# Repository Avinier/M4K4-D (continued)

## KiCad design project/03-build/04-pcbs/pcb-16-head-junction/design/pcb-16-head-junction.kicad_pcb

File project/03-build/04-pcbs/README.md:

# 04 — PCBs

This folder holds the schematic, layout, fabrication and electrical-validation work for the robot's custom boards. It is a work area, not a fabrication release. Part records stay in the [project BOM](../BOM.csv); every selection and change goes in the [build decisions](../decisions.md). It replaces the former `04-custom-pcb/` folder ([D-038](../decisions.md#d-038)).

Each custom board is designed, procured and integrated into the final CAD one at a time, in its own `pcb-NN-name/` folder. [workflow.md](workflow.md) describes the three stages and tracks each board's progress.

## Tools

Chosen in [D-058](../decisions.md#d-058); layout tool and routing changed by [D-060](../decisions.md#d-060).

| Tool | Used for | Where |
|---|---|---|
| KiCad 10.99 (nightly) + KiPy | Schematic and layout, driven through KiPy and computer-use tools; the GUI for review | `/Applications/KiCad-nightly` (build 20261024, `de08734017`), side by side with 10.0.6 in `/Applications/KiCad`. KiPy (`kicad-python` 0.8.0) in `~/.local/share/kipy/venv`; it talks to the running GUI, and the nightly has no bundled `pcbnew` Python. Each board's project is in its folder's `design/` |
| `kicad-cli` (same install as the layout) | ERC, DRC with the schematic-to-board check, Gerbers, drill, pick-and-place, BOM, board STEP, renders | `/Applications/KiCad-nightly/KiCad.app/Contents/MacOS/kicad-cli` (10.99). The 10.0.6 CLI in `/Applications/KiCad` may not read files the nightly saved |
| [`tools/kp.py`](tools/kp.py) | KiPy layout helpers: place (restores 3D models after a flip), octolinear tracks, vias, audit, DRC. Steps in [design-playbook.md](design-playbook.md) | Run with `~/.local/share/kipy/venv/bin/python` against the open PCB editor |
| JLCPCB (default), PCBWay, Lion Circuits (MII service) | PCB fabrication and assembly (PCBA). These three only. Layouts follow the [fab-neutral rules](#fab-neutral-design-rules), and the fab is chosen by quote ([D-062](../decisions.md#d-062)) | — |
| text-to-cad (cadgen) | Stage 3: the board STEP placed in the robot CAD | Project runtime 0.4.28 (see [final/v1](../final/v1/README.md)) |

## Layout rules

These rules take priority over D-058 ([D-060](../decisions.md#d-060); builder, 2026-10-14). They come from someone else's experience of LLM-driven KiCad layout. When an LLM lays out a board, it must:

1. use KiCad 10.99 (the nightly build, which adds scripting features) and drive it through KiPy and computer-use tools;
2. not use an autorouter such as Freerouting;
3. place components one at a time or in small functional groups;
4. adjust placement after routing where that helps;
5. route with octolinear traces, organised into buses of parallel, equally spaced tracks. Plan fanouts first. Keep detours and roundabout routes to a minimum, especially on signal nets. Size track widths and pours for each net's current. Optionally, write reusable scripts that check these properties and use them to check the work.

## Fab-neutral design rules

Only three fabs make Makad boards: **JLCPCB** (China, the default), **PCBWay** (China) and **Lion Circuits** (Bengaluru), on its **MII** (Make in India) service ([D-062](../decisions.md#d-062), builder, 2026-10-25). Every board is laid out so that any of the three can make it on its standard service, with no layout change. The rule set is the strictest standard 2-layer, 1 oz limit of the three. Each board carries it as a KiCad custom rules file, `design/<board>.kicad_dru`, copied from [PCB-15's](pcb-15-nose-hall/design/pcb-15-nose-hall.kicad_dru). The fab is chosen by quote at procure.

| Rule | Fab-neutral minimum | JLCPCB | PCBWay | Lion Circuits MII |
|---|---|---|---|---|
| Track width and copper gap | **0.16 mm** | 0.10 | 0.10 | 0.152 (6 mil) |
| Via | **0.35 mm hole, 0.67 mm pad** (ring 0.16) | hole 0.15, pad 0.25 | hole 0.15, ring 0.15 | drill 0.35, ring 0.152 |
| Via to other copper | **0.31 mm**, from the via's copper and from its hole | — | — | 12 mil (0.305), via to trace |
| Hole to hole | **0.31 mm** | — | — | 12 mil between vias |
| Copper to routed edge | **0.3 mm** | 0.2 | 0.25 | 0.3 |
| Solder-mask web between pads | **0.16 mm** | 0.10 | not stated; confirm | 0.152 |
| Silkscreen text | **1.0 mm high, 0.16 mm line**, or leave silkscreen off | 1.0 | 0.8 | 0.58, line 0.152 |
| Board thickness tolerance | **State it on the order** when the mounting needs it | ±10 % | ±10 % at 1.0 mm and thicker; confirm below | ±10 % |
| Assembly, minimum board | **Panelise** small boards | 10 × 10 mm | quote; 0402 parts get an engineering review | 50 × 100 mm |

Lion's page lists three services. **MII** is the target. **Custom** is looser (0.25 mm drill, 10 mil via spacing), so an MII layout also suits it. **Rush** is tighter (0.4 mm drill, 8 mil tracks, 14 mil via spacing) and is not a target. A board that needs Rush is checked against it first.

Sources, read 2026-10-25: [JLCPCB](https://jlcpcb.com/capabilities/pcb-capabilities), [PCBWay](https://www.pcbway.com/capabilities.html), [Lion Circuits](https://lioncircuits.com/pcb-manufacturing-capabilities). Read the pages again before each order. If a fab tightens a limit, tighten the rule here first.

## Board register

**[D-093](../decisions.md#d-093) (2026-11-06):** PCB-02, 03, 04, 05, 06 and 07 are replaced by bought modules and PCB-13 is deleted. After D-107 the custom boards are PCB-08, 09, 10, 11, 12 and 15, plus PCB-17 from D-117 (**seven designs**). The superseded rows are kept as the record. The change map is in [simplification-plan.md](../simplification-plan.md).

| ID | Board | Location | BOM | Status | Work still required |
|---|---|---|---|---|---|
| PCB-01 | 2S pack protection | Chassis tub, on the pack | CH-023 | **Bought:** Robocraze TIFPS0629 ([D-019](../decisions.md#d-019)); the RP-02 custom design is reference only | Bench acceptance before cells: [power-boards.md §3](power-boards.md#3-pcb-01--tifps0629-acceptance-before-cells-are-connected) |
| PCB-02 | Charger (BQ25798), on/off latch, pack sense, `ENERGY_OK` | Body, behind the rear panel (vertical) | CH-041 | **Superseded by [D-093](../decisions.md#d-093): bought.** A pushbutton power switch module and an INA226/219 voltage/current monitor; no charger (the pack is charged outside the robot). Rev A routing archived in the [board folder](pcb-02-charger/README.md) | Module selection and India stock ([plan level 3](../simplification-plan.md#7-levels-of-work)) |
| PCB-03 | Motor gate, permit chain, head 5 V rail, drive feeds | Body, above the tub | CH-042 | **Superseded by [D-093](../decisions.md#d-093): bought.** Two buck-boost modules: head pitch/roll 5.5 V and yaw 11.1 V. Drive feeds come straight from the switched bus with the SMBJ8.5A and bulk at each `VM`; the yaw servo plug moves to PCB-08 | Module selection and India stock |
| PCB-04 | Five branch converters (C2, base, Pi, display, audio) | Body, under the compute tray | CH-043 | **Superseded by [D-093](../decisions.md#d-093): bought.** Two Pololu S13V30F5 5 V buck-boost modules ([D-094](../decisions.md#d-094)): one for the Pi, one shared by C3, amp, C2 and display | Module selection and India stock; series Schottky in `W11` (C3 USB back-feed) |
| PCB-05 | Audio front end (MAX98357A, 2 × ADAU7002) | Body, above the Pi, hung from the frame on three M2 SMT spacers ([D-067](../decisions.md#d-067)) | BO-002 | **Superseded by [D-093](../decisions.md#d-093): bought.** MAX98357A breakout (BO-007, promoted from bench) and an audio hub. Rev A archived in the [board folder](pcb-05-audio-front-end/README.md) | Amp mount in CAD; four-mic I²S overlay on the bench |
| PCB-06 ×4 | PDM microphone board | Body shell bosses | BO-005 | **Superseded by [D-093](../decisions.md#d-093): bought.** Four I²S mic breakouts with an L/R pin (INMP441 class), two per lane on SDI0/SDI1. Rev A archived in the [board folder](pcb-06-pdm-mic/README.md) | Boss redesign for the breakout outline; overlay bench test before the shell is printed |
| PCB-07 | Base IMU (ICM-42688-P) | Chassis | CH-021 | **Superseded by [D-093](../decisions.md#d-093): bought.** SPI 6-axis IMU breakout on the existing `J10-7` pinout, on a printed adapter on the J15A holes | Breakout selection; adapter in CAD |
| PCB-08 | W47 body junction, D-107 | Body under yaw plate | CH-083 | **Rev B draft, do not order**: Micro-Fit2×3 and GH6 replace both FFC sockets; 34×25mm, four layers; ERC0/0, pin audit12/12, W47 audit5/5, DRC0 errors/0 unconnected/0 parity (six explained library warnings) | Populated fit, cradle/service checks and physical release gates in [board record](pcb-08-yaw-junction/README.md) |
| PCB-14 | **Superseded by [D-107](../decisions.md#d-107), do not order.** Yaw rotor joiner boards ([D-052](../decisions.md#d-052); replaces the D-044 Ø35 ring): three identical vertical 0.8 mm boards (a fourth identical board joins the CSI on the [D-105](../decisions.md#d-105) camera-loop bracket), each a straight-through 22-pin 0.5 mm FFC joiner ([D-101](../decisions.md#d-101): lower contact *n* → upper 23 − *n*) with a down-facing FH34SRJ for its cassette FFC (`W37`/`W42`/`W43`) and an up-facing one for the head FFC, both on the +Y face; 4.5 mm pitch (D-101); tabs seat in the rotor posts | Body, inside the rotating yaw hub (Z 133.9–150.7) | BO-062 (×3) | Rev A draft (do not order) | FH34SRJ sample: open-actuator height (`E` 3.4 mm); fold mock-up at the 4.5 mm planes; standard-mini CSI end in FH34SRJ and the BO-050 CSI test; CSI Pi-end conductor 1 when the drop is drawn; stage-3 board replacement |
| PCB-09 | C0 link adapter (2 × RS-422, audio pass-through, enclosure-fan switch `J9-4`) | Body, on the Pi header, on two M2.5 × 11 standoffs at Pi holes 3/4 | CH-084 | **Rev B routed and CAD fitted on `pcb-09-revB`; not released** ([D-092](../decisions.md#d-092), [D-098 amendment](../decisions.md#d-098)): Samtec SSW-120-01-T-D socket, 4 layers, retained rev A functions and connector pinouts, plus J6 six-net button/OFF/INA226 `i2c-gpio` service interface; [board folder](pcb-09-c0-link-adapter/README.md). Final CAD uses the rev B STEP | Nightly DRC 0/0/0, fit 8/8, mount 7/7 and final integration PASS. `fab/revB` is a draft; wait for #2813, Pi-image and populated bench acceptance before the D-064 order. CR-02 boot/overlay and fan current, socket seating, contact check and harness pull test remain |
| PCB-10 | C3 controller carrier (watchdog, READY, sleep gate, Hall and TCRT circuits) | Body, −Y side wall | CH-044 | **Inputs frozen** ([D-068](../decisions.md#d-068), [board folder](pcb-10-c3-carrier/README.md)): two screws and two printed edge hooks, Espressif DevKitC-1 v1.1 only, TPS3436CCCBG from Mouser India, GPIO map v0.2, `J10-2` named by direction ; [KiCad geometry installed in final CAD](../final/v1/README.md#pcb-geometry-in-the-whole-robot-assembly) | **Design done, rev A** (four layers; DRC clean; `check_pcb10_fit.py` 7/7; [fab outputs](pcb-10-c3-carrier/fab/revA/README.md)); GPIO map v0.3, `J10-2` in U2's order; U2/U3 from Mouser India, consigned; nose, TCRT and head-riser harness re-routes at stage 3; [D-093](../decisions.md#d-093): `J10-12` is unused (PCB-03 is gone) and `W11` gets a series Schottky against USB back-feed; no re-spin |
| PCB-11 | Status LED carrier (WS2812B-2020-V6, 100 nF, 330 Ω in DIN) | Head crown, in the socket fused inside the crown ([D-065](../decisions.md#d-065)) | CH-085 | **Rev A designed** ([D-065](../decisions.md#d-065)); [board folder](pcb-11-status-led/README.md) ; [KiCad geometry installed in final CAD](../final/v1/README.md#pcb-geometry-in-the-whole-robot-assembly) | Procure: panel (with PCB-15), two-sided assembly quote, passive MPNs, V6 from the fab (C52917434) or an RFQ to Hubtronics; brightness, stray-light and light-bleed bench (G03) |
| PCB-12 | C2 head carrier (ESP32-S3-Zero, servo bus, head-link and display transceivers) | Head, roll frame, in place of the C2 tray | CH-086 | **Rev A draft (do not order)** ([D-102](../decisions.md#d-102)): signals only on three GH headers; head grounds join here through 0 Ω links; replaces the tray's front wall, two M2 screws into crossbar bosses; fit 7/7 through the roll/pitch envelope | Received Zero pad/pin check; ST3215-HS bus levels (B5); the head-harness FFC-to-wire break; stage-3 board replacement |
| PCB-15 | Nose Hall carrier (DRV5055A3, decoupling, output filter, three wire pads); numbered by [D-057](../decisions.md#d-057), formerly listed by its BOM ID | Chassis nose, in the pod-seat slot | CH-064 | **Rev A designed** ([D-013](../decisions.md#d-013), [D-059](../decisions.md#d-059), [D-063](../decisions.md#d-063)); [nose-hall-board.md](../01-chassis/v1/research/nose-hall-board.md); [board folder](pcb-15-nose-hall/README.md) ; [KiCad geometry installed in final CAD](../final/v1/README.md#pcb-geometry-in-the-whole-robot-assembly) | Procure: panel, two-sided assembly quote, passive MPNs; cap trip and wire-break fault bench |
| PCB-16 | **Superseded by [D-107](../decisions.md#d-107), do not order.** Head junction: passive FFC-to-wire break for the W42/W43 head FFCs (two FH34SRJ, per-net wire pads) ([D-103](../decisions.md#d-103)) | Head, flat on the yaw disc beside the +Y leg foot | CH-111 | **Rev A draft (do not order)**: historical fit7/7; removed from final CAD by D107 | Wire-bundle routes across pitch and roll; CSI path; FFC strip mock-up; pad sizes against received wire |
| PCB-17 | Balance-tap fuse cards ×2 (three 1206 1 A very-fast fuses, wire pads) | Chassis tub, on the PCB-01 BMS ends under CH-106 reliefs | CH-103 | **Rev A designed** ([D-117](../decisions.md#d-117)); [board folder](pcb-17-balance-fuse-cards/README.md): ERC 0/0, audit 13/13, parity DRC 0/0/0; two 0.8 mm cards, 6 × 9 and 9.5 × 10 mm | Procure: panel with PCB-11/15; received HW-391 pad and height check; N5 with the cards potted |
| PCB-13 | Charge inlet: GCT USB4140, TVS2200, ESDA25W, STUSB4500, input P-FET | Body, rear-panel pad (comes off with the panel) | BO-015 | **Deleted by [D-093](../decisions.md#d-093).** The pack is charged outside the robot through rear-panel charge and balance ports. Rev A archived in the [board folder](pcb-13-charge-inlet/README.md) | — |

Power-board specification (superseded by [D-093](../decisions.md#d-093) except the DRV8833 facts, the `VM` TVS and the TIFPS0629 acceptance): the RP-02 [board-specs.md](../../02-prototypes/RP-02-electrical/board-specs.md) is the read-only reference, and [power-boards.md](power-boards.md) holds what the build changes. The charge path, from the USB-C inlet to the pack entry, is in [charge-path.md](charge-path.md). Open board work without another home is tracked in [open-items.md](open-items.md).

## Rules

The board outlines in CAD are packaging assumptions. They imply no Gerbers, completed schematic or passed board test.

Basic chassis fit and controlled motor tests can use a regulated bench supply, a development controller, driver boards and a temporary harness. Hall and bare-TCRT circuits can be prototyped separately. Full custom-board fabrication is not a prerequisite for those tests. Battery-powered and integrated sensor/control tests keep their protection, interface and validation requirements.

Before releasing any board, record:

- its exact revision, schematic, BOM and layout;
- connector pinout, protection and enable behaviour;
- mounting dimensions and fabrication/assembly outputs;
- measured electrical results.

When an interface changes, update the affected CAD and the canonical BOM.

**Droid CAD changes go in [final/v1/cad](../final/v1/cad/) only** (builder, 2026-10-14). Envelope fixes, board STEPs that replace placeholders, and the mounting features they need are made in `makad-v1.step.py`. For example, `DROID_CUTS` cuts material from printed parts, `DROID_ADDS` adds it and `DROID_MOVES` shifts parts ([D-063](../decisions.md#d-063)). They are not made in the chassis, body or head sources. The subsystem checks don't see these changes, so each one gets its own targeted check script in `final/v1/cad` (for example `check_pcb15_relief.py`, [D-059](../decisions.md#d-059)).

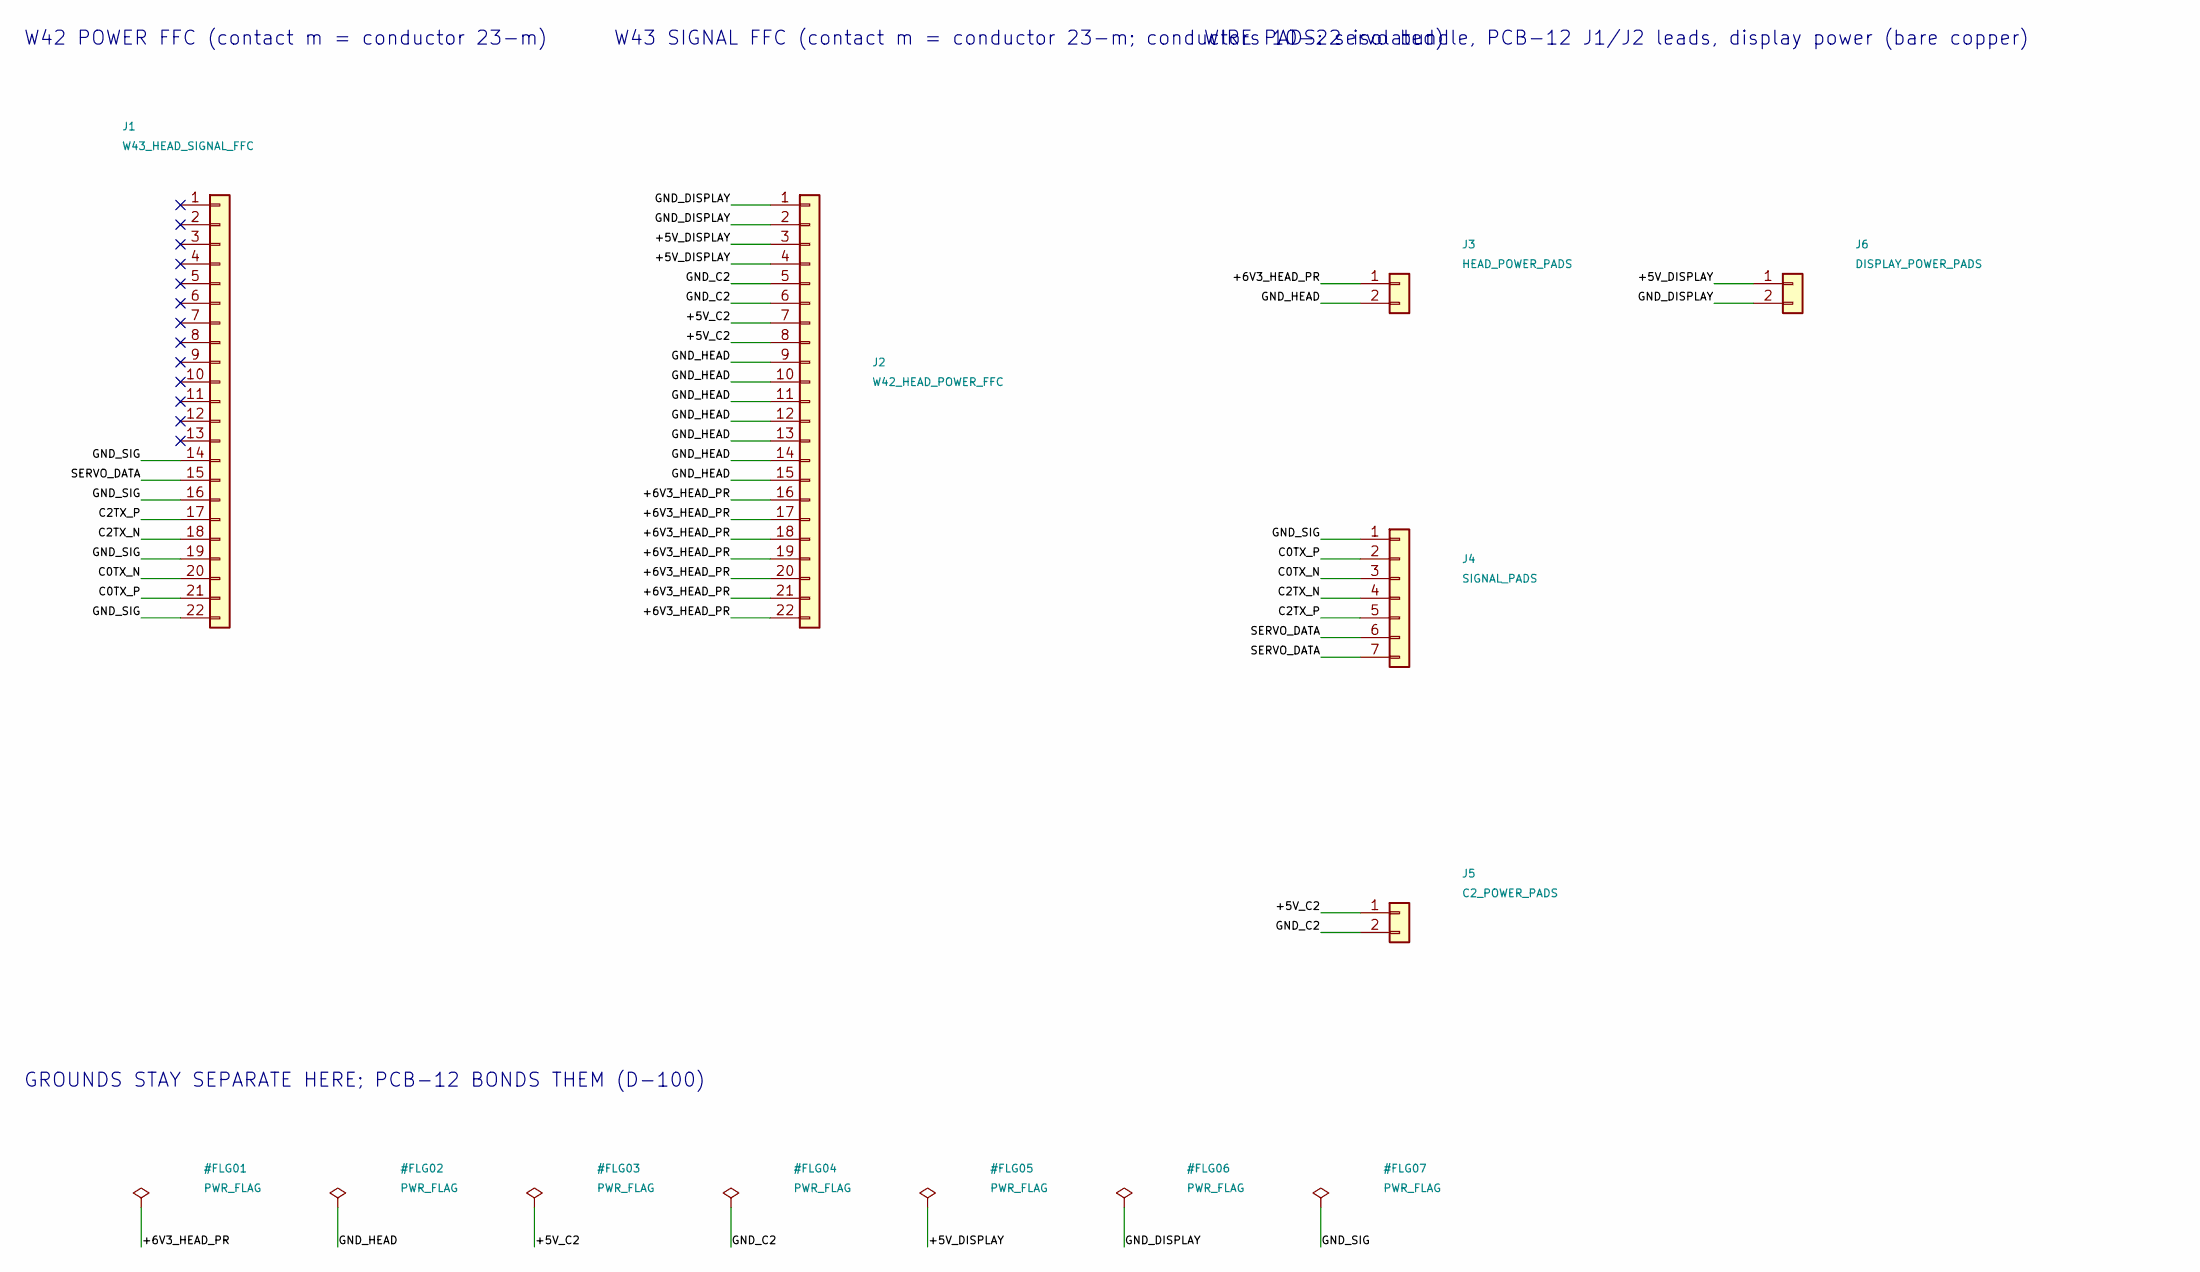
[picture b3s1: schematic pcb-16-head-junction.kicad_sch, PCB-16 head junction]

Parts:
J1: W43_HEAD_SIGNAL_FFC; Hirose_FH34SRJ-22S-0.5SH_1x22_P0.50mm
J2: W42_HEAD_POWER_FFC; Hirose_FH34SRJ-22S-0.5SH_1x22_P0.50mm
J3: HEAD_POWER_PADS; WirePads_Power_1x02_P3.5mm
J4: SIGNAL_PADS; WirePads_1x07_P1.5mm
J5: C2_POWER_PADS; WirePads_1x02_P1.5mm
J6: DISPLAY_POWER_PADS; WirePads_1x02_P1.5mm

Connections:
/+5V_C2: J2.7, J2.8, J5.1
/+5V_DISPLAY: J2.3, J2.4, J6.1
/+6V3_HEAD_PR: J2.16, J2.17, J2.18, J2.19, J2.20, J2.21, J2.22, J3.1
/C0TX_N: J1.20, J4.3
/C0TX_P: J1.21, J4.2
/C2TX_N: J1.18, J4.4
/C2TX_P: J1.17, J4.5
/GND_C2: J2.5, J2.6, J5.2
/GND_DISPLAY: J2.1, J2.2, J6.2
/GND_HEAD: J2.9, J2.10, J2.11, J2.12, J2.13, J2.14, J2.15, J3.2
/GND_SIG: J1.14, J1.16, J1.19, J1.22, J4.1
/SERVO_DATA: J1.15, J4.6, J4.7

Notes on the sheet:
W42 POWER FFC (contact m = conductor 23-m)
W43 SIGNAL FFC (contact m = conductor 23-m; conductors 10-22 isolated)
WIRE PADS: servo bundle, PCB-12 J1/J2 leads, display power (bare copper)
GROUNDS STAY SEPARATE HERE; PCB-12 BONDS THEM (D-100)

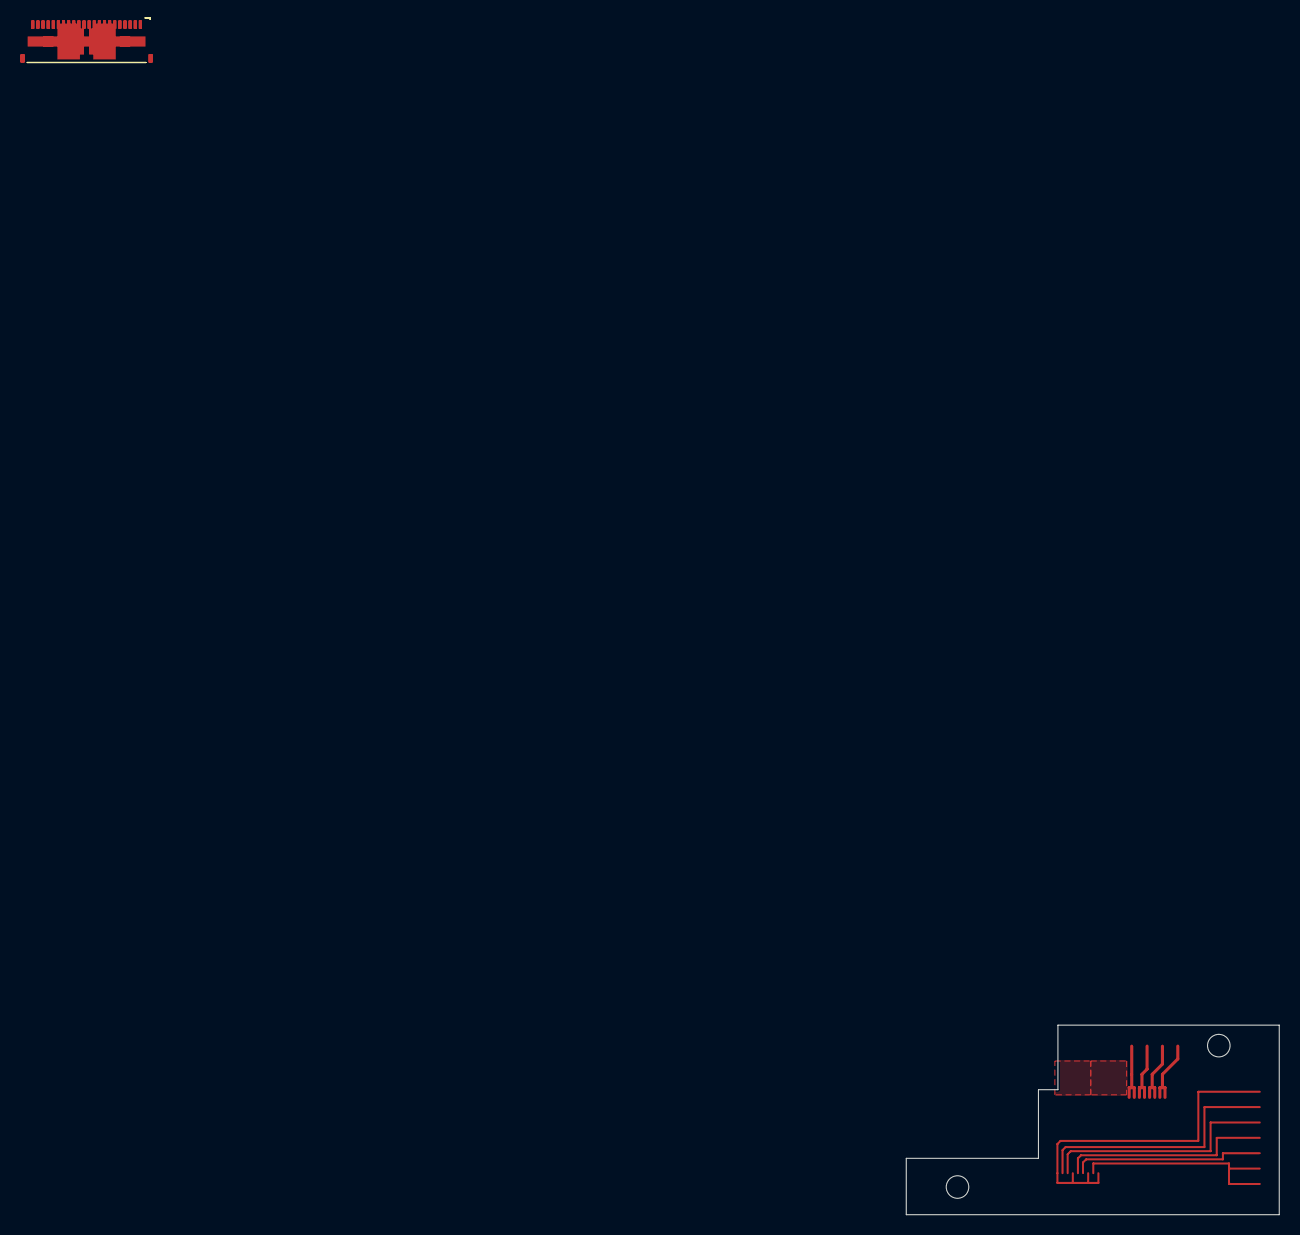
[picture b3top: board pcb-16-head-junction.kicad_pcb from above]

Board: 2 copper layers, 36.4 x 18.5 mm, 6 parts (0 on the bottom side), 12 nets.

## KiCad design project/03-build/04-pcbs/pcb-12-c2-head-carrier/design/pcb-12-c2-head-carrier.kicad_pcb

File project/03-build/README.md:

# 03 — Build

Turn the [prototype decisions](../02-prototypes/) into parts that can be printed, assembled, measured, and revised. This phase is complete when the built robot passes its integration tests, not when the CAD looks finished.

## Status (2026-11-12)

The build follows the [D-093](decisions.md#d-093) simplification: bought power modules replace the charger, motor-gate, converter, audio, mic and IMU boards. Progress by level is in the [simplification plan §7](simplification-plan.md#7-levels-of-work).

- **Modules** selected ([D-094](decisions.md#d-094), [module-selection.md](module-selection.md)) and **ordered 2026-11-08**; each still has a bench gate (N1–N12).
- **Droid CAD** for the modules, ports and mounts is done ([D-095](decisions.md#d-095)); the chassis front module and the D-095 mount prints are re-exported to [04-print](../04-print/01-chassis/README.md) ([D-099](decisions.md#d-099)).
- **Harness**: [05-harness](05-harness/README.md) is **released for build with conditions** ([D-108](decisions.md#d-108), lifting the [D-096](decisions.md#d-096) electrical HOLD): W02P balance taps stay unbuilt until CH-103 protection, no R010 in the switched-bus path, and one closed-body M1 heat check at first power-up.
- **Custom boards** ([04-pcbs](04-pcbs/README.md)): Seven custom designs: PCB-08/09 rev B, PCB-10/11/12/15 rev A and PCB-17 rev A (CH-103 balance-tap fuse cards, D-117). PCB-14/16 are superseded. [D-107](head-umbilical-plan.md) uses twelve loose wires and stripped HDMI pairs through the yaw axis, two B0091 adapters, and the restored D-051 pivot. Draft fabrication and physical acceptance remain HOLD. See the [execution evidence](final/v1/d107-execution.md).
- **BOM**: [BOM.csv](BOM.csv) is reconciled to D-093–D-097; the subsystem BOM snapshots still predate D-093.

## Where things are

| Record | Holds |
|---|---|
| [decisions.md](decisions.md) | The ledger: every decision, part selection, BOM change and CAD edit |
| [BOM.csv](BOM.csv) | The single parts register |
| [BOM-deliveries.md](BOM-deliveries.md) | What has physically arrived, mapped to BOM rows, with problems found |
| [TODO.md](TODO.md) | Open ordering, receiving and release actions |
| [simplification-plan.md](simplification-plan.md) | The D-093 change map, levels of work and bench register (N-tests) |
| [module-selection.md](module-selection.md) | Bought modules (M1–M13) and their acceptance gates |
| [01-chassis](01-chassis/), [02-body](02-body/), [03-head](03-head/) | Subsystem specs, BOM snapshots and subsystem-only CAD |
| [04-pcbs](04-pcbs/README.md) | Custom board register, design workflow and playbook |
| [04-software](04-software/firmware-requirements.md) | Firmware requirements (low-battery stop, button-off, servo limits, mics) |
| [05-harness](05-harness/README.md) | Connectors, cables, pinouts and service breaks |
| [final/v1](final/v1/README.md) | The whole-robot CAD and its checks, plus the [print guide](final/v1/printguide.md) |

Printing (lab, workflow, coupons, per-part print settings) is in [04-print](../04-print/README.md).

## Governing context

**From 2026-09-28, `03-build/` governs.** Record every new decision, part selection, BOM change and CAD edit here, in the subsystem and version folder it belongs to, and log it in [`decisions.md`](decisions.md).

[`02-prototypes/`](../02-prototypes/) and its RP folders, including RP-03 locomotion and RP-06 CAD, are **read-only reference**. Link to them for earlier research, gates and evidence; do not add decisions to them or edit their CAD. Where an RP document disagrees with `03-build/`, `03-build/` wins.

Each subsystem's `cad/` holds only that subsystem. The whole robot is in [`final/v1/cad/`](final/v1/README.md), and droid-level changes (envelope fixes, cuts, bought-part STEPs) go there with a targeted check.

## BOM conventions

[BOM.csv](BOM.csv) is the single parts register. Subsystem `BOM.md` files are dated working snapshots, not fabrication releases; refresh them deliberately after a BOM change.

In the register, `DESIGN` means custom geometry exists, `CANDIDATE` means a part or family is proposed, `SELECTED` means the build choice is settled with receiving and physical verification still separate, `OPEN` means the design needs a choice before release, and `HOLD` means do not order or fabricate until its blocker is resolved. `SUPERSEDED` rows are kept for history. `supplier_candidate` is a lead to verify, not a stock claim. Update `procurement` and `received_measurements` with order and caliper evidence; do not infer receipt from CAD or an old availability check.

## Build order

1. [Chassis and locomotion](01-chassis/): wheels, drive, supports and the body mounting interface. Test with representative body and head mass and centre of mass.
2. [Body](02-body/): load-bearing frame, packaging, power and wiring, access, cooling and the head support. Recheck its effect on the chassis.
3. [Head](03-head/): build and test the mechanism on its real body support. Part selection and isolated joint tests can start earlier.
4. [Full droid](final/v1/README.md): assemble the subsystems and rerun whole-robot motion, power, thermal, fault and interaction tests.

Work can overlap. Freeze only the interfaces needed for the next release, and record changes that affect another subsystem. Unreleased custom boards do not block isolated chassis fit or controlled external-supply tests.

## What a version means

`v1`, `v2`, `v3`, and later folders are **build iterations**. Each version aims to produce a **print-ready build release** for its defined scope, followed by a physical build and test. A version is not called production-ready before its printed article passes its tests.

Each release needs only these records:

1. **Scope and interfaces** — parts included, assumed loads and mass, dimensions that other subsystems depend on, and known exclusions.
2. **BOM and procurement** — exact purchased parts, quantities, sources, status, and measured dimensions. Keep one project BOM; capture the version's exact BOM as a release snapshot so subsystem lists cannot silently diverge.
3. **Fabrication package** — source CAD and revision, printable exports, material, printer/process settings, orientation, supports, tolerances, inserts, and assembly instructions. Measure received hardware and correct dependent CAD before releasing custom parts.
4. **Test plan and evidence** — focused stress-test research, expected loads, measurable pass/fail criteria set before scored tests, test setup, results, photos/logs, and failures. Mark unrun tests **OPEN**, not passed.
5. **Exit decision** — `PASS`, `ITERATE`, or `HOLD`, with the evidence and the specific change needed. A failed or improved design becomes the next version; a passing subsystem can move forward while its shared interfaces remain tracked.

For the chassis, test at least fit and retention, loaded stiffness, wheel runout, traction and turning, braking and tipping, support/skid behaviour, motor temperature, and service access. Use representative worst-case body/head ballast until those assemblies exist. Reuse the [RP-03 locomotion gates](../02-prototypes/RP-03-locomotion/gates.md) and [RP-06 open items](../02-prototypes/RP-06-cad/TODO.md) as inputs; register relevant numeric limits and test conditions before scoring a run.

The working loop is **select → order → measure → update CAD → release → print/assemble → test → record → iterate or lock**. `LOCKED` means the built article passed its defined tests and its interfaces are controlled. A CAD check or paper calculation alone does not lock a part.

## Documentation rule

Keep these pages shorter and more decisive than [02-prototypes](../02-prototypes/). Link to existing research instead of copying it. State the current decision, revision, evidence, open risk, and next action; remove abandoned options from the active build instructions. Do not call estimates measurements or let a later CAD edit silently change a released version.

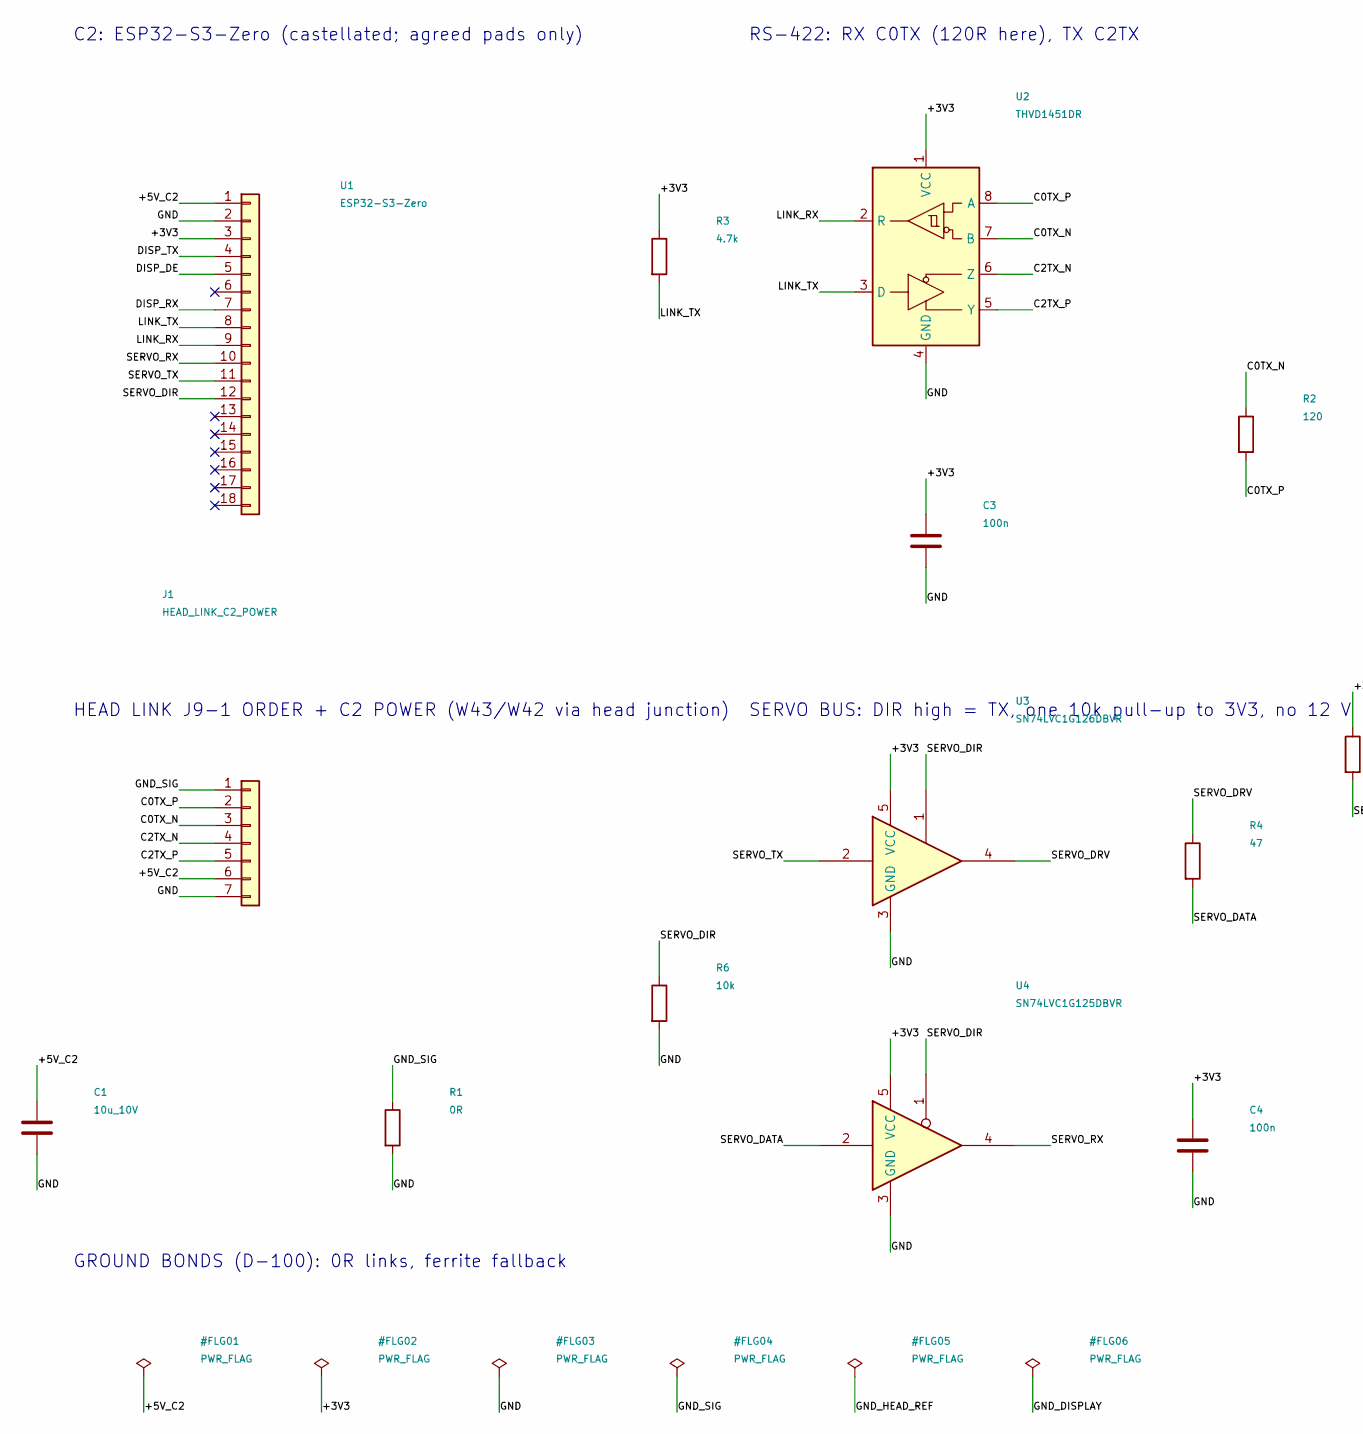
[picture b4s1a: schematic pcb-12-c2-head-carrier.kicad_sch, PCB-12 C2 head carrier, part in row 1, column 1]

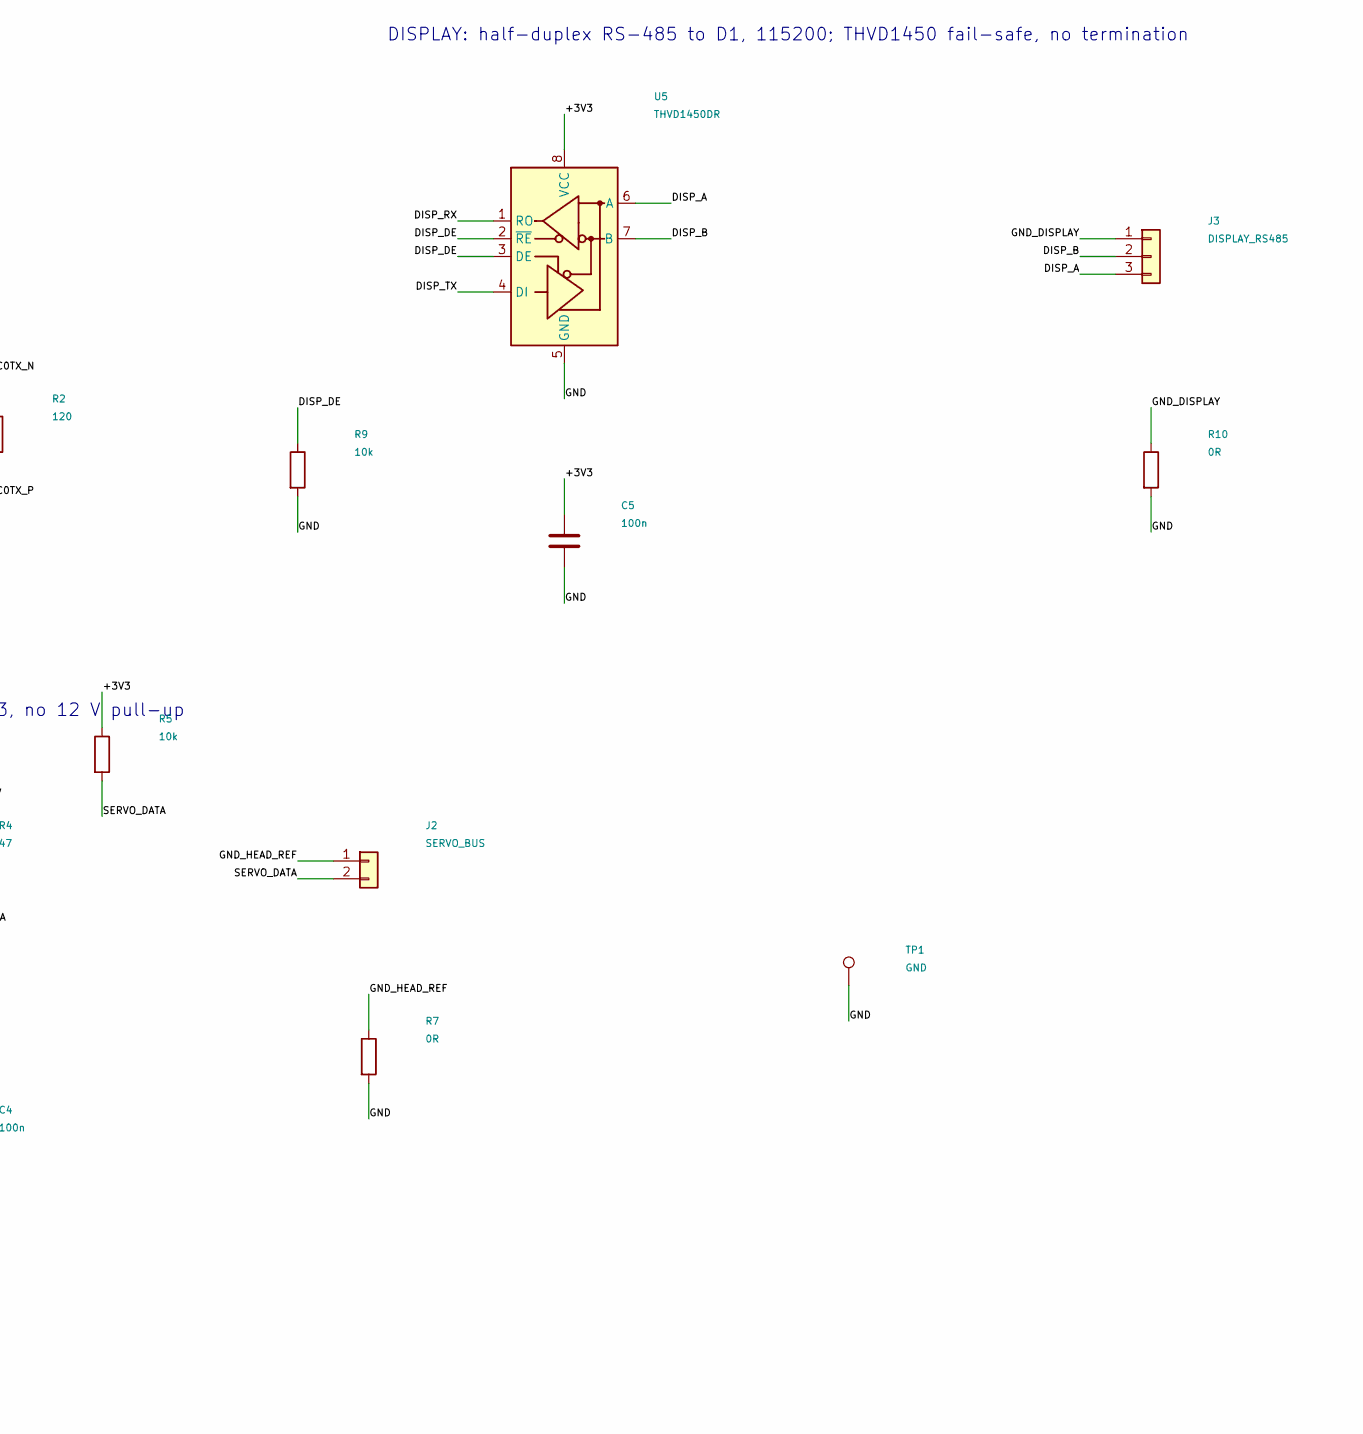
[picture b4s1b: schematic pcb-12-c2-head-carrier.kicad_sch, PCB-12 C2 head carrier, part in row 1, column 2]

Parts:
C1: 10u_10V; C_0805_2012Metric
C3, C4, C5: 100n; C_0603_1608Metric
J1: HEAD_LINK_C2_POWER; JST_GH_BM07B-GHS-TBT_1x07-1MP_P1.25mm_Vertical
J2: SERVO_BUS; JST_GH_BM02B-GHS-TBT_1x02-1MP_P1.25mm_Vertical
J3: DISPLAY_RS485; JST_GH_BM03B-GHS-TBT_1x03-1MP_P1.25mm_Vertical
R1, R7, R10: 0R; R_0603_1608Metric
R2: 120; R_0603_1608Metric
R3: 4.7k; R_0603_1608Metric
R4: 47; R_0603_1608Metric
R5, R6, R9: 10k; R_0603_1608Metric
TP1: GND; TestPoint_Pad_D1.0mm
U1: ESP32-S3-Zero; Waveshare_ESP32-S3-Zero_Castellated
U2: THVD1451DR; SOIC-8_3.9x4.9mm_P1.27mm
U3: SN74LVC1G126DBVR; SOT-23-5
U4: SN74LVC1G125DBVR; SOT-23-5
U5: THVD1450DR; SOIC-8_3.9x4.9mm_P1.27mm

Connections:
/+3V3: C3.1, C4.1, C5.1, R3.1, R5.1, U1.3, U2.1, U3.5, U4.5, U5.8
/+5V_C2: C1.1, J1.6, U1.1
/C0TX_N: J1.3, R2.1, U2.7
/C0TX_P: J1.2, R2.2, U2.8
/C2TX_N: J1.4, U2.6
/C2TX_P: J1.5, U2.5
/DISP_A: J3.3, U5.6
/DISP_B: J3.2, U5.7
/DISP_DE: R9.1, U1.5, U5.2, U5.3
/DISP_RX: U1.7, U5.1
/DISP_TX: U1.4, U5.4
/GND: C1.2, C3.2, C4.2, C5.2, J1.7, R1.2, R6.2, R7.2, R9.2, R10.2, TP1.1 (Pin_1_1), U1.2, U2.4, U3.3, U4.3, U5.5
/GND_DISPLAY: J3.1, R10.1
/GND_HEAD_REF: J2.1, R7.1
/GND_SIG: J1.1, R1.1
/LINK_RX: U1.9, U2.2
/LINK_TX: R3.2, U1.8, U2.3
/SERVO_DATA: J2.2, R4.2, R5.2, U4.2
/SERVO_DIR: R6.1, U1.12, U3.1, U4.1
/SERVO_DRV: R4.1, U3.4
/SERVO_RX: U1.10, U4.4
/SERVO_TX: U1.11, U3.2

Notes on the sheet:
C2: ESP32-S3-Zero (castellated; agreed pads only)
HEAD LINK J9-1 ORDER + C2 POWER (W43/W42 via head junction)
RS-422: RX C0TX (120R here), TX C2TX
SERVO BUS: DIR high = TX, one 10k pull-up to 3V3, no 12 V pull-up
DISPLAY: half-duplex RS-485 to D1, 115200; THVD1450 fail-safe, no termination
GROUND BONDS (D-100): 0R links, ferrite fallback

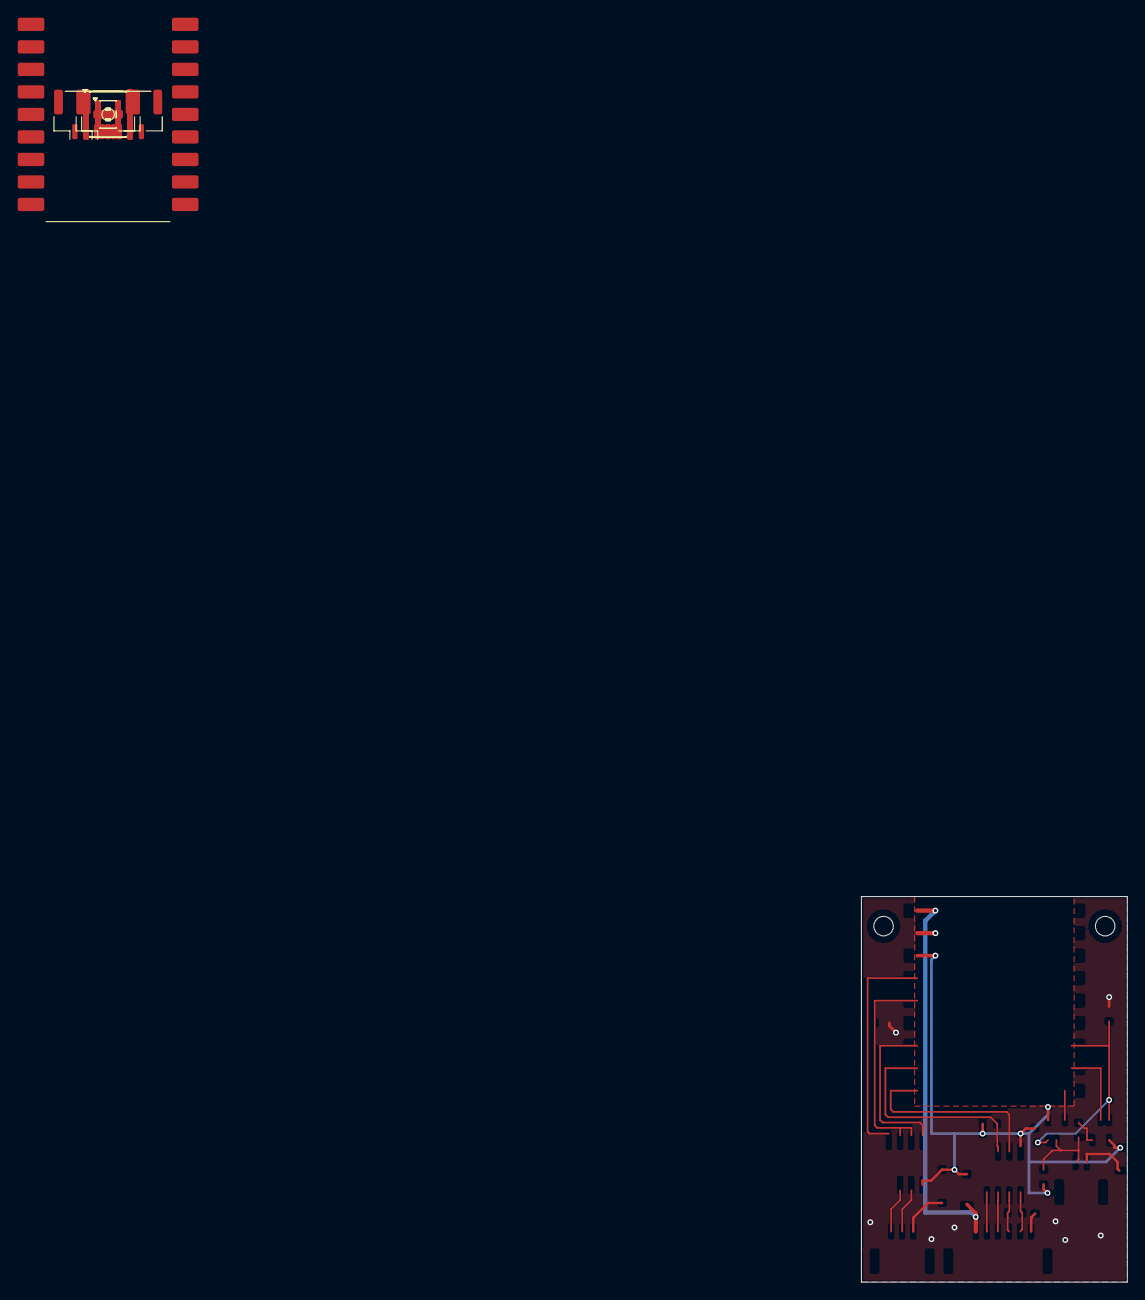
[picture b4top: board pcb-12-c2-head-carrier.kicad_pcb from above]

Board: 2 copper layers, 30.0 x 43.5 mm, 22 parts (0 on the bottom side), 22 nets.

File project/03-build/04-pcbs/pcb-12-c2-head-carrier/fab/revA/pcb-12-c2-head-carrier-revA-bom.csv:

"Comment","Designator","Footprint","Quantity","MPN","Manufacturer","LCSC Part #"
"10u_10V","C1","Capacitor_SMD:C_0805_2012Metric","1","CL21A106KPFNNNE","Samsung",""
"100n","C3,C4,C5","Capacitor_SMD:C_0603_1608Metric","3","CC0603KRX7R9BB104","Yageo",""
"HEAD_LINK_C2_POWER","J1","Connector_JST:JST_GH_BM07B-GHS-TBT_1x07-1MP_P1.25mm_Vertical","1","BM07B-GHS-TBT(LF)(SN)(N)","JST",""
"SERVO_BUS","J2","Connector_JST:JST_GH_BM02B-GHS-TBT_1x02-1MP_P1.25mm_Vertical","1","BM02B-GHS-TBT(LF)(SN)(N)","JST",""
"DISPLAY_RS485","J3","Connector_JST:JST_GH_BM03B-GHS-TBT_1x03-1MP_P1.25mm_Vertical","1","BM03B-GHS-TBT(LF)(SN)(N)","JST",""
"0R","R1,R7,R10","Resistor_SMD:R_0603_1608Metric","3","RC0603JR-070RL","Yageo",""
"120","R2","Resistor_SMD:R_0603_1608Metric","1","RC0603FR-07120RL","Yageo",""
"4.7k","R3","Resistor_SMD:R_0603_1608Metric","1","RC0603FR-074K7L","Yageo",""
"47","R4","Resistor_SMD:R_0603_1608Metric","1","RC0603FR-0747RL","Yageo",""
"10k","R5,R6,R9","Resistor_SMD:R_0603_1608Metric","3","RC0603FR-0710KL","Yageo",""
"ESP32-S3-Zero","U1","pcb12:Waveshare_ESP32-S3-Zero_Castellated","1","ESP32-S3-Zero (SKU 25081, without header)","Waveshare",""
"THVD1451DR","U2","Package_SO:SOIC-8_3.9x4.9mm_P1.27mm","1","THVD1451DR","TI",""
"SN74LVC1G126DBVR","U3","Package_TO_SOT_SMD:SOT-23-5","1","SN74LVC1G126DBVR","TI",""
"SN74LVC1G125DBVR","U4","Package_TO_SOT_SMD:SOT-23-5","1","SN74LVC1G125DBVR","TI",""
"THVD1450DR","U5","Package_SO:SOIC-8_3.9x4.9mm_P1.27mm","1","THVD1450DR","TI",""
